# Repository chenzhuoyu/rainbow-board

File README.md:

# rainbow-board
ECP5 FPGA breakout board for Colorlight i5 / i9

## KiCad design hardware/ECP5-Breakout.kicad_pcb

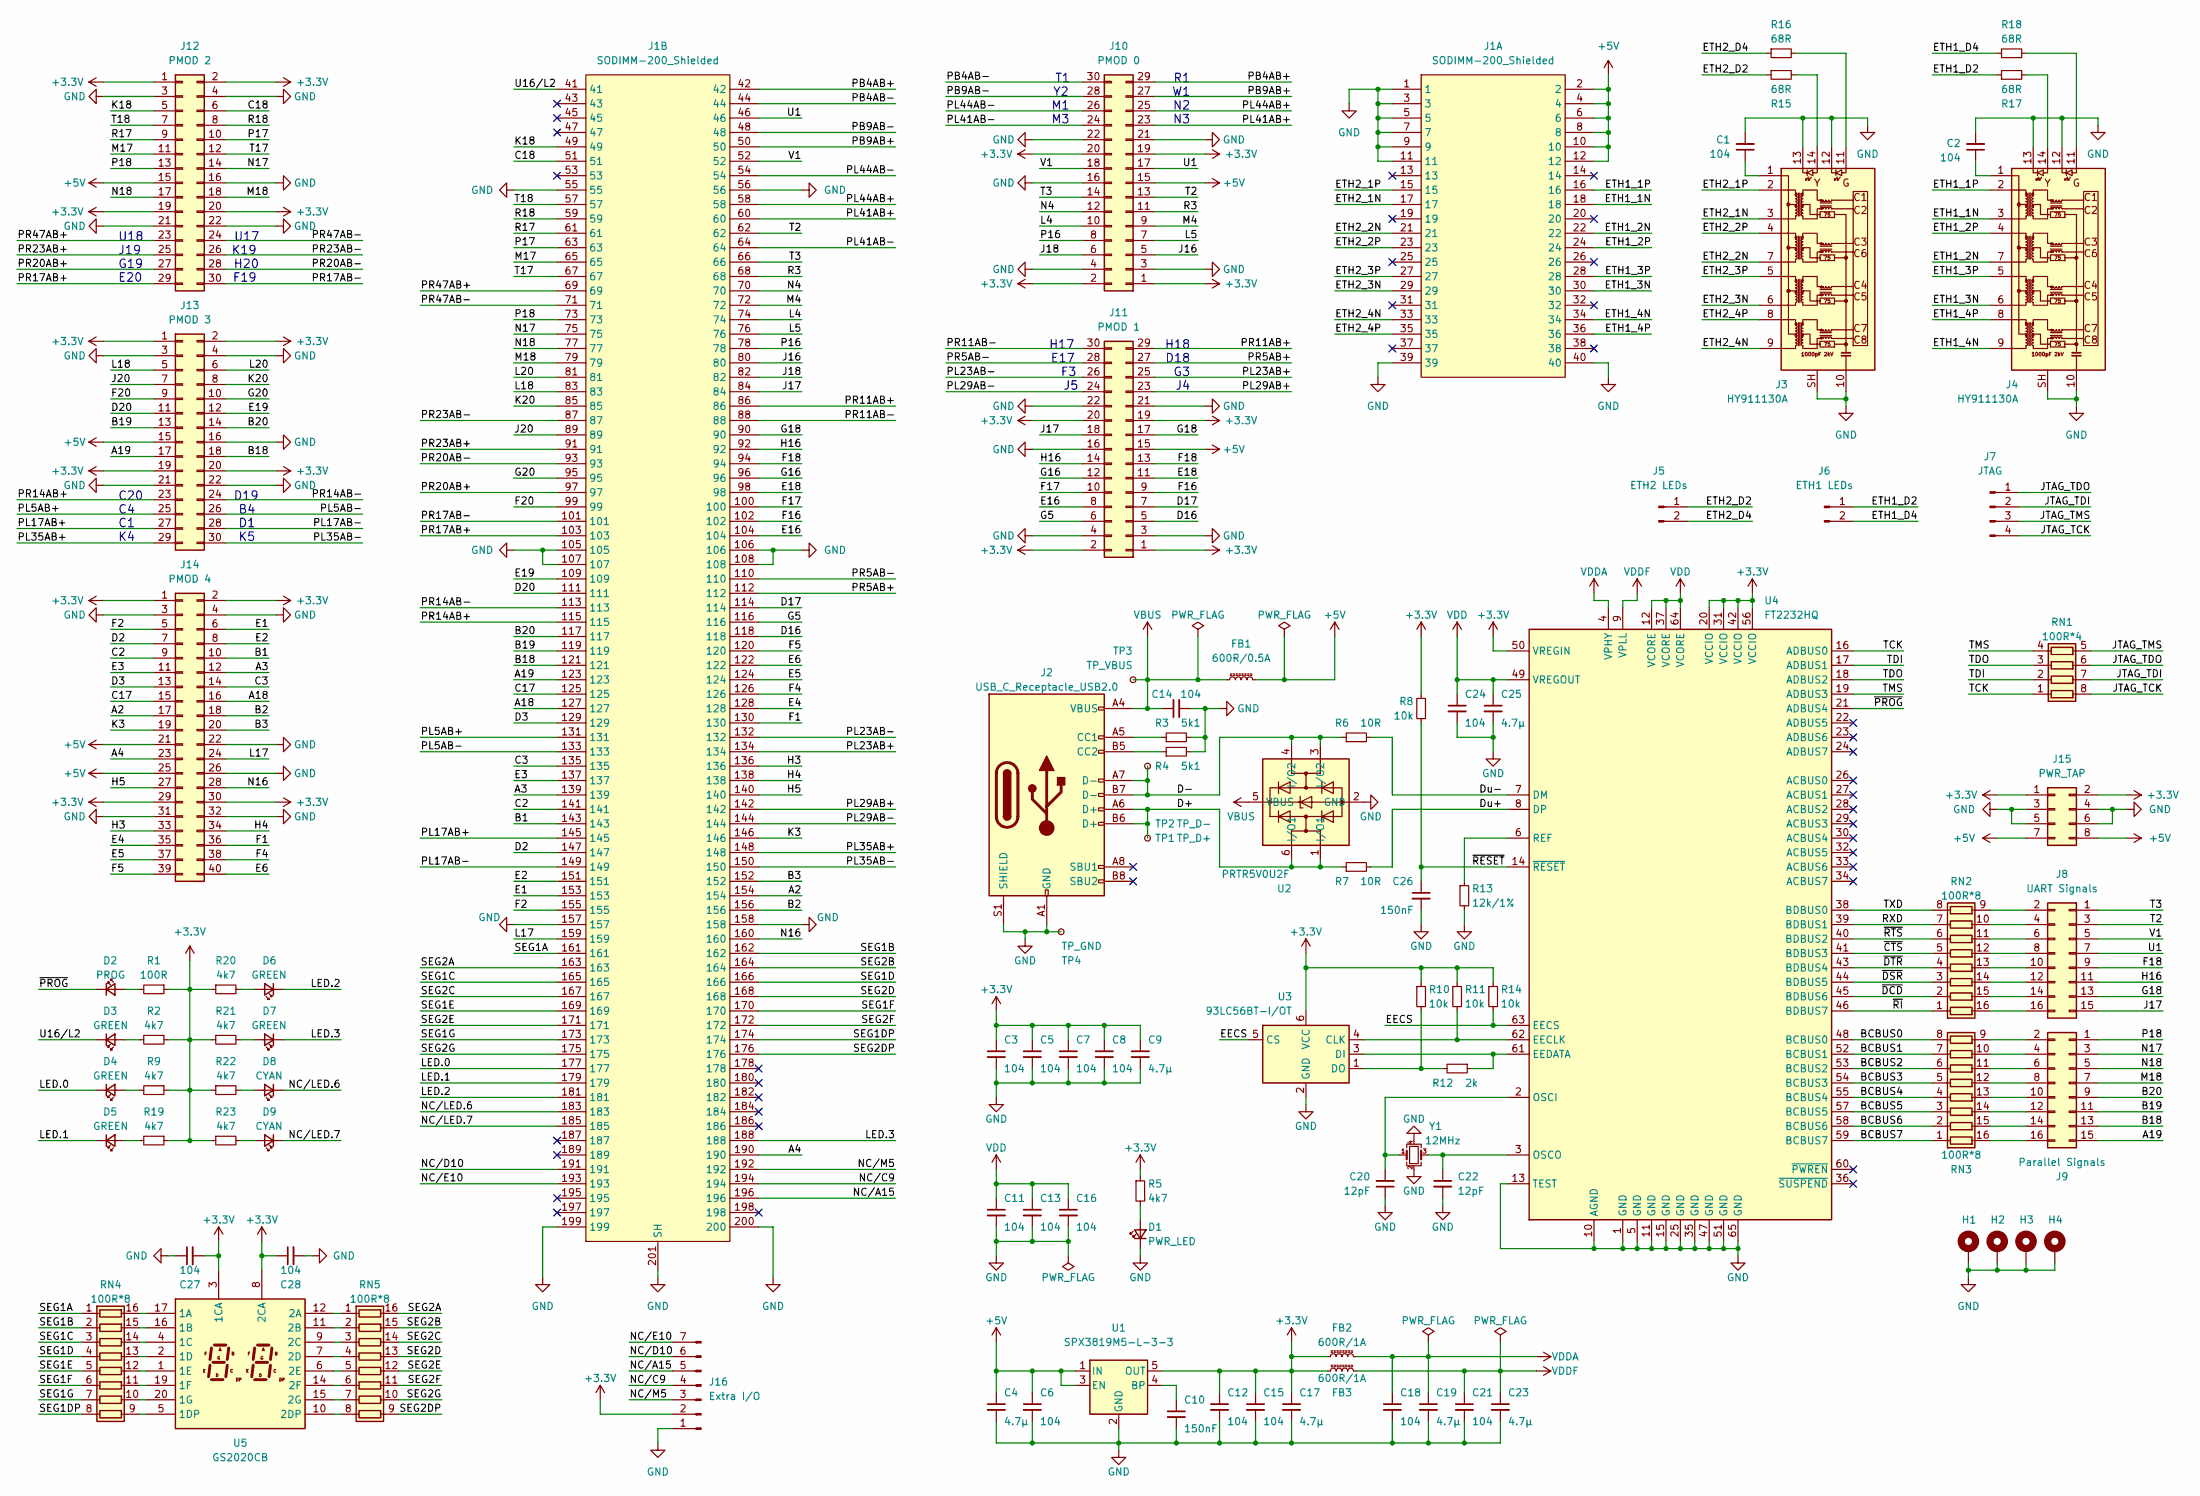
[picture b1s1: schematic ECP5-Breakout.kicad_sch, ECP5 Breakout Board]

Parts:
C1, C2, C3, C5, C6, C7, C8, C11, C12, C13, C14, C15, C16, C18, C21, C24, C27, C28: 104; C_0603_1608Metric
C4, C9, C17, C19, C23, C25: 4.7µ; CP_EIA-3216-10_Kemet-I
C10, C26: 150nF; C_0402_1005Metric
C20, C22: 12pF; C_0402_1005Metric
D1: PWR_LED; LED_0805_2012Metric
D2: PROG; LED_0805_2012Metric
D3: GREEN; LED_0805_2012Metric
D4, D5, D6, D7: GREEN; LED_0603_1608Metric
D8, D9: CYAN; LED_0603_1608Metric
FB1: 600R/0.5A; L_0603_1608Metric
FB2, FB3: 600R/1A; L_0603_1608Metric
H1, H2, H3, H4: MountingHole_Pad; MountingHole_3.2mm_M3_Pad_Via
J1: SODIMM-200_Shielded; 1473149-4_SODIMM_200P_H5.2_DDR2
J2: USB_C_Receptacle_USB2.0; USB_C_Receptacle_HRO_TYPE-C-31-M-12
J3, J4: HY911130A
J5: ETH2 LEDs; PinHeader_1x02_P2.54mm_Vertical
J6: ETH1 LEDs; PinHeader_1x02_P2.54mm_Vertical
J7: JTAG; PinHeader_1x04_P2.54mm_Vertical
J8: UART Signals; PinHeader_2x08_P2.54mm_Vertical
J9: Parallel Signals; PinHeader_2x08_P2.54mm_Vertical
J10: PMOD 0; PinSocket_2x15_P2.54mm_Horizontal
J11: PMOD 1; PinSocket_2x15_P2.54mm_Horizontal
J12: PMOD 2; PinSocket_2x15_P2.54mm_Horizontal
J13: PMOD 3; PinSocket_2x15_P2.54mm_Horizontal
J14: PMOD 4; PinSocket_2x20_P2.54mm_Horizontal
J15: PWR_TAP; PinHeader_2x04_P2.54mm_Vertical
J16: Extra I/O; PinHeader_1x07_P2.54mm_Vertical
R1: 100R; R_0402_1005Metric
R2, R5, R9, R19, R20, R21, R22, R23: 4k7; R_0402_1005Metric
R3, R4: 5k1; R_0402_1005Metric
R6, R7: 10R; R_0402_1005Metric
R8, R10, R11, R14: 10k; R_0402_1005Metric
R12: 2k; R_0402_1005Metric
R13: 12k/1%; R_0402_1005Metric
R15, R16, R17, R18: 68R; R_0402_1005Metric
RN1: 100R*4; R_Array_Concave_4x0402
RN2, RN3, RN4, RN5: 100R*8; R_Array_Convex_8x0602
TP1: TP_D+; TestPoint_Pad_D1.0mm
TP2: TP_D-; TestPoint_Pad_D1.0mm
TP3: TP_VBUS; TestPoint_Pad_D1.0mm
TP4: TP_GND; TestPoint_Pad_D1.0mm
U1: SPX3819M5-L-3-3; SOT-23-5
U2: PRTR5V0U2F; SOT-886
U3: 93LC56BT-I/OT; SOT-23-6
U4: FT2232HQ; QFN-64-1EP_9x9mm_P0.5mm_EP4.35x4.35mm
U5: GS2020CB
Y1: 12MHz; Crystal_SMD_2520-4Pin_2.5x2.0mm

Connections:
+3.3V: C3.1, C5.1, C7.1, C8.1, C9.1, C12.1, C15.1, C17.1, C27.2, C28.1, FB2.1, FB3.1, J10.1, J10.2, J10.19, J10.20, J11.1, J11.2, J11.19, J11.20, J12.1, J12.2, J12.19, J12.20, J13.1, J13.2, J13.19, J13.20, J14.1, J14.2, J14.29, J14.30, J15.1, J15.2, J16.2, R1.1, R2.1, R5.1, R8.1, R9.1, R10.1, R11.1, R14.1, R19.1, R20.1, R21.1, R22.1, R23.1, U1.5 (OUT), U3.6 (VCC), U4.20 (VCCIO), U4.31 (VCCIO), U4.42 (VCCIO), U4.50 (VREGIN), U4.56 (VCCIO), U5.3 (1CA), U5.8 (2CA), U5.13 (2CA), U5.18 (1CA)
+5V: C4.1, C6.1, FB1.2, J1.2, J1.4, J1.6, J1.8, J1.10, J1.12, J10.15, J11.15, J12.15, J13.15, J14.21, J14.25, J15.7, J15.8, U1.1 (IN), U1.3 (EN)
/A2: J1.154, J14.17
/A3: J1.139, J14.12
/A4: J1.190, J14.23
/A18: J1.127, J14.16
/A19: J1.123, J9.15, J13.17
/B1: J1.143, J14.10
/B2: J1.156, J14.18
/B3: J1.152, J14.20
/B18: J1.121, J9.13, J13.18
/B19: J1.119, J9.11, J13.13
/B20: J1.117, J9.9, J13.14
/BCBUS0: RN3.8 (R8.1), U4.48 (BCBUS0)
/BCBUS1: RN3.7 (R7.1), U4.52 (BCBUS1)
/BCBUS2: RN3.6 (R6.1), U4.53 (BCBUS2)
/BCBUS3: RN3.5 (R5.1), U4.54 (BCBUS3)
/BCBUS4: RN3.4 (R4.1), U4.55 (BCBUS4)
/BCBUS5: RN3.3 (R3.1), U4.57 (BCBUS5)
/BCBUS6: RN3.2 (R2.1), U4.58 (BCBUS6)
/BCBUS7: RN3.1 (R1.1), U4.59 (BCBUS7)
/C2: J1.141, J14.9
/C3: J1.135, J14.14
/C17: J1.125, J14.15
/C18: J1.51, J12.6
/D2: J1.147, J14.7
/D3: J1.129, J14.13
/D16: J1.118, J11.5
/D17: J1.114, J11.7
/D20: J1.111, J13.11
/D+: J2.A6 (D+), J2.B6 (D+), R7.1, TP1.1, U2.1 (I/O1), U2.6 (I/O1)
/D-: J2.A7 (D-), J2.B7 (D-), R6.1, TP2.1, U2.3 (I/O2), U2.4 (I/O2)
/Du+: R7.2, U4.8 (DP)
/Du-: R6.2, U4.7 (DM)
/E1: J1.153, J14.6
/E2: J1.151, J14.8
/E3: J1.137, J14.11
/E4: J1.128, J14.35
/E5: J1.124, J14.37
/E6: J1.122, J14.40
/E16: J1.104, J11.8
/E18: J1.98, J11.11
/E19: J1.109, J13.12
/EECS: R14.2, U3.5 (CS), U4.63 (EECS)
/ETH1_1N: J1.18, J4.3 (TD1-)
/ETH1_1P: J1.16, J4.2 (TD1+)
/ETH1_2N: J1.22, J4.7 (TD2-)
/ETH1_2P: J1.24, J4.4 (TD2+)
/ETH1_3N: J1.30, J4.6 (TD3-)
/ETH1_3P: J1.28, J4.5 (TD3+)
/ETH1_4N: J1.34, J4.9 (TD4-)
/ETH1_4P: J1.36, J4.8 (TD4+)
/ETH1_D2: J6.1, R17.1
/ETH1_D4: J6.2, R18.1
/ETH2_1N: J1.17, J3.3 (TD1-)
/ETH2_1P: J1.15, J3.2 (TD1+)
/ETH2_2N: J1.21, J3.7 (TD2-)
/ETH2_2P: J1.23, J3.4 (TD2+)
/ETH2_3N: J1.29, J3.6 (TD3-)
/ETH2_3P: J1.27, J3.5 (TD3+)
/ETH2_4N: J1.33, J3.9 (TD4-)
/ETH2_4P: J1.35, J3.8 (TD4+)
/ETH2_D2: J5.1, R15.1
/ETH2_D4: J5.2, R16.1
/F1: J1.130, J14.36
/F2: J1.155, J14.5
/F4: J1.126, J14.38
/F5: J1.120, J14.39
/F16: J1.102, J11.9
/F17: J1.100, J11.10
/F18: J1.94, J8.9, J11.13
/F20: J1.99, J13.9
/G5: J1.116, J11.6
/G16: J1.96, J11.12
/G18: J1.90, J8.13, J11.17
/G20: J1.95, J13.10
/H3: J1.136, J14.33
/H4: J1.138, J14.34
/H5: J1.140, J14.27
/H16: J1.92, J8.11, J11.14
/J16: J1.80, J10.5
/J17: J1.84, J8.15, J11.18
/J18: J1.82, J10.6
/J20: J1.89, J13.7
/JTAG_TCK: J7.4, RN1.8 (R1.2)
/JTAG_TDI: J7.2, RN1.7 (R2.2)
/JTAG_TDO: J7.1, RN1.6 (R3.2)
/JTAG_TMS: J7.3, RN1.5 (R4.2)
/K3: J1.146, J14.19
/K18: J1.49, J12.5
/K20: J1.85, J13.8
/L4: J1.74, J10.10
/L5: J1.76, J10.7
/L17: J1.159, J14.24
/L18: J1.83, J13.5
/L20: J1.81, J13.6
/LED.0: D4.1 (K), J1.177
/LED.1: D5.1 (K), J1.179
/LED.2: D6.1 (K), J1.181
/LED.3: D7.1 (K), J1.188
/M4: J1.72, J10.9
/M17: J1.65, J12.11
/M18: J1.79, J9.7, J12.18
/N4: J1.70, J10.12
/N16: J1.160, J14.28
/N17: J1.75, J9.3, J12.14
/N18: J1.77, J9.5, J12.17
/NC/A15: J1.196, J16.5
/NC/C9: J1.194, J16.4
/NC/D10: J1.191, J16.6
/NC/E10: J1.193, J16.7
/NC/LED.6: D8.1 (K), J1.183
/NC/LED.7: D9.1 (K), J1.185
/NC/M5: J1.192, J16.3
/P16: J1.78, J10.8
/P17: J1.63, J12.10
/P18: J1.73, J9.1, J12.13
/PB4AB+: J1.42, J10.29
/PB4AB-: J1.44, J10.30
/PB9AB+: J1.50, J10.27
/PB9AB-: J1.48, J10.28
/PL5AB+: J1.131, J13.25
/PL5AB-: J1.133, J13.26
/PL17AB+: J1.145, J13.27
/PL17AB-: J1.149, J13.28
/PL23AB+: J1.134, J11.25
/PL23AB-: J1.132, J11.26
/PL29AB+: J1.142, J11.23
/PL29AB-: J1.144, J11.24
/PL35AB+: J1.148, J13.29
/PL35AB-: J1.150, J13.30
/PL41AB+: J1.60, J10.23
/PL41AB-: J1.64, J10.24
/PL44AB+: J1.58, J10.25
/PL44AB-: J1.54, J10.26
/PR5AB+: J1.112, J11.27
/PR5AB-: J1.110, J11.28
/PR11AB+: J1.86, J11.29
/PR11AB-: J1.88, J11.30
/PR14AB+: J1.115, J13.23
/PR14AB-: J1.113, J13.24
/PR17AB+: J1.103, J12.29
/PR17AB-: J1.101, J12.30
/PR20AB+: J1.97, J12.27
/PR20AB-: J1.93, J12.28
/PR23AB+: J1.91, J12.25
/PR23AB-: J1.87, J12.26
/PR47AB+: J1.69, J12.23
/PR47AB-: J1.71, J12.24
/R3: J1.68, J10.11
/R17: J1.61, J12.9
/R18: J1.59, J12.8
/RXD: RN2.7 (R7.1), U4.39 (BDBUS1)
/SEG1A: J1.161, RN4.1 (R1.1)
/SEG1B: J1.162, RN4.2 (R2.1)
/SEG1C: J1.165, RN4.3 (R3.1)
/SEG1D: J1.166, RN4.4 (R4.1)
/SEG1DP: J1.174, RN4.8 (R8.1)
/SEG1E: J1.169, RN4.5 (R5.1)
/SEG1F: J1.170, RN4.6 (R6.1)
/SEG1G: J1.173, RN4.7 (R7.1)
/SEG2A: J1.163, RN5.16 (R1.2)
/SEG2B: J1.164, RN5.15 (R2.2)
/SEG2C: J1.167, RN5.14 (R3.2)
/SEG2D: J1.168, RN5.13 (R4.2)
/SEG2DP: J1.176, RN5.9 (R8.2)
/SEG2E: J1.171, RN5.12 (R5.2)
/SEG2F: J1.172, RN5.11 (R6.2)
/SEG2G: J1.175, RN5.10 (R7.2)
/T2: J1.62, J8.3, J10.13
/T3: J1.66, J8.1, J10.14
/T17: J1.67, J12.12
/T18: J1.57, J12.7
/TCK: RN1.1 (R1.1), U4.16 (ADBUS0)
/TDI: RN1.2 (R2.1), U4.17 (ADBUS1)
/TDO: RN1.3 (R3.1), U4.18 (ADBUS2)
/TMS: RN1.4 (R4.1), U4.19 (ADBUS3)
/TXD: RN2.8 (R8.1), U4.38 (BDBUS0)
/U1: J1.46, J8.7, J10.17
/U16/L2: D3.1 (K), J1.41
/V1: J1.52, J8.5, J10.18
/~CTS: RN2.5 (R5.1), U4.41 (BDBUS3)
/~DCD: RN2.2 (R2.1), U4.45 (BDBUS6)
/~DSR: RN2.3 (R3.1), U4.44 (BDBUS5)
/~DTR: RN2.4 (R4.1), U4.43 (BDBUS4)
/~PROG: D2.1 (K), U4.21 (ADBUS4)
/~RESET: C26.1, R8.2, U4.14 (~RESET)
/~RI: RN2.1 (R1.1), U4.46 (BDBUS7)
/~RTS: RN2.6 (R6.1), U4.40 (BDBUS2)
GND: C1.2, C2.2, C3.2, C4.2, C5.2, C6.2, C7.2, C8.2, C9.2, C10.2, C11.2, C12.2, C13.2, C14.2, C15.2, C16.2, C17.2, C18.2, C19.2, C20.1, C21.2, C22.2, C23.2, C24.2, C25.2, C26.2, C27.1, C28.2, D1.1 (K), H1.1, H2.1, H3.1, H4.1, J1.1, J1.3, J1.5, J1.7, J1.9, J1.11, J1.39, J1.40, J1.55, J1.56, J1.105, J1.106, J1.107, J1.108, J1.157, J1.158, J1.199, J1.200, J1.201 (SH), J2.A1 (GND), J2.A12 (GND), J2.B1 (GND), J2.B12 (GND), J2.S1 (SHIELD), J3.10 (GND), J3.12, J3.13, J3.SH, J4.10 (GND), J4.12, J4.13, J4.SH, J10.3, J10.4, J10.16, J10.21, J10.22, J11.3, J11.4, J11.16, J11.21, J11.22, J12.3, J12.4, J12.16, J12.21, J12.22, J13.3, J13.4, J13.16, J13.21, J13.22, J14.3, J14.4, J14.22, J14.26, J14.31, J14.32, J15.3, J15.4, J15.5, J15.6, J16.1, R3.2, R4.2, R13.2, TP4.1, U1.2 (GND), U2.2 (GND), U3.2 (GND), U4.1 (GND), U4.5 (GND), U4.10 (AGND), U4.11 (GND), U4.13 (TEST), U4.15 (GND), U4.25 (GND), U4.35 (GND), U4.47 (GND), U4.51 (GND), U4.65 (GND), Y1.2, Y1.4
unnamed: D1.2 (A), R5.2
unnamed: D2.2 (A), R1.2
unnamed: D3.2 (A), R2.2
unnamed: D4.2 (A), R9.2
unnamed: D5.2 (A), R19.2
unnamed: D6.2 (A), R20.2
unnamed: D7.2 (A), R21.2
unnamed: D8.2 (A), R22.2
unnamed: D9.2 (A), R23.2
unnamed: J2.A5 (CC1), R3.1
unnamed: J2.B5 (CC2), R4.1
unnamed: C1.1, J3.1 (CT)
unnamed: J3.11, R16.2
unnamed: J3.14, R15.2
unnamed: C2.1, J4.1 (CT)
unnamed: J4.11, R18.2
unnamed: J4.14, R17.2
unnamed: J8.2, RN2.9 (R8.2)
unnamed: J8.4, RN2.10 (R7.2)
unnamed: J8.6, RN2.11 (R6.2)
unnamed: J8.8, RN2.12 (R5.2)
unnamed: J8.10, RN2.13 (R4.2)
unnamed: J8.12, RN2.14 (R3.2)
unnamed: J8.14, RN2.15 (R2.2)
unnamed: J8.16, RN2.16 (R1.2)
unnamed: J9.2, RN3.9 (R8.2)
unnamed: J9.4, RN3.10 (R7.2)
unnamed: J9.6, RN3.11 (R6.2)
unnamed: J9.8, RN3.12 (R5.2)
unnamed: J9.10, RN3.13 (R4.2)
unnamed: J9.12, RN3.14 (R3.2)
unnamed: J9.14, RN3.15 (R2.2)
unnamed: J9.16, RN3.16 (R1.2)
unnamed: RN4.16 (R1.2), U5.17 (1A)
unnamed: RN4.15 (R2.2), U5.16 (1B)
unnamed: RN4.14 (R3.2), U5.4 (1C)
unnamed: RN4.13 (R4.2), U5.2 (1D)
unnamed: RN4.12 (R5.2), U5.1 (1E)
unnamed: RN4.11 (R6.2), U5.19 (1F)
unnamed: RN4.10 (R7.2), U5.20 (1G)
unnamed: RN4.9 (R8.2), U5.5 (1DP)
unnamed: RN5.1 (R1.1), U5.12 (2A)
unnamed: RN5.2 (R2.1), U5.11 (2B)
unnamed: RN5.3 (R3.1), U5.9 (2C)
unnamed: RN5.4 (R4.1), U5.7 (2D)
unnamed: RN5.5 (R5.1), U5.6 (2E)
unnamed: RN5.6 (R6.1), U5.14 (2F)
unnamed: RN5.7 (R7.1), U5.15 (2G)
unnamed: RN5.8 (R8.1), U5.10 (2DP)
unnamed: C10.1, U1.4 (BP)
unnamed: R11.2, U3.4 (CLK), U4.62 (EECLK)
unnamed: R12.1, U3.3 (DI), U4.61 (EEDATA)
unnamed: R10.2, R12.2, U3.1 (DO)
unnamed: C20.2, U4.2 (OSCI), Y1.1
unnamed: C22.1, U4.3 (OSCO), Y1.3
unnamed: R13.1, U4.6 (REF)
VBUS: C14.1, FB1.1, J2.A4 (VBUS), J2.A9 (VBUS), J2.B4 (VBUS), J2.B9 (VBUS), TP3.1, U2.5 (VBUS)
VDD: C11.1, C13.1, C16.1, C24.1, C25.1, U4.12 (VCORE), U4.37 (VCORE), U4.49 (VREGOUT), U4.64 (VCORE)
VDDA: C18.1, C19.1, FB2.2, U4.4 (VPHY)
VDDF: C21.1, C23.1, FB3.2, U4.9 (VPLL)

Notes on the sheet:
H17 H18 E17 D18 F3 G3 J5 J4
U18 U17 J19 K19 G19 H20 E20 F19
T1 R1 Y2 W1 M1 N2 M3 N3
C20 D19 C4 B4 C1 D1 K4 K5

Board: 4 copper layers, 98 parts (4 on the bottom side), 250 nets, no tracks yet.

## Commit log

2023-03-19 chore: add schematics & pcb
2023-03-19 chore: add board images
2023-03-25 fix: relocate pogo-pins
2023-04-01 feat: fix ethernet led pogo pins
2023-04-13 chore: reversed all pins for i9
2023-04-30 wip: new revision
2023-05-29 feat: add new components
